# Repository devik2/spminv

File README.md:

# spminv

Simple IGBT motor inverter

Initial idea was independent but in 2024 when I started I borrowed
idea of heatsink from from STMBL project.

There are differences from STMBL, only one MCU located on power N potential,
1xCAN,2xRS422 RX and 2xRS485 RX/TX for encoder/communications and separated
by galvanical isolators.

Flyback power supply for 15V/3V3 on N side and 5V for isolated side. Thus only
input is 90-350V DC.
This is because my main usage is for spindle motors where driver is located near
spindle and not in remote cabinet.

Why not use STMBL ? I wanted to use different IPM, integrate it into CAN network
of my homemade CNC and to play with FOC by myself. 
And I already use my 60V BLDC driver for 3 years and started this "upgrade" before
I found STMBL.

[And have to say, I'd stay with 60V mosfet inverter but it is hard to find quality(!)
 motors. All low ripple hi-torque I found are 200V rated]

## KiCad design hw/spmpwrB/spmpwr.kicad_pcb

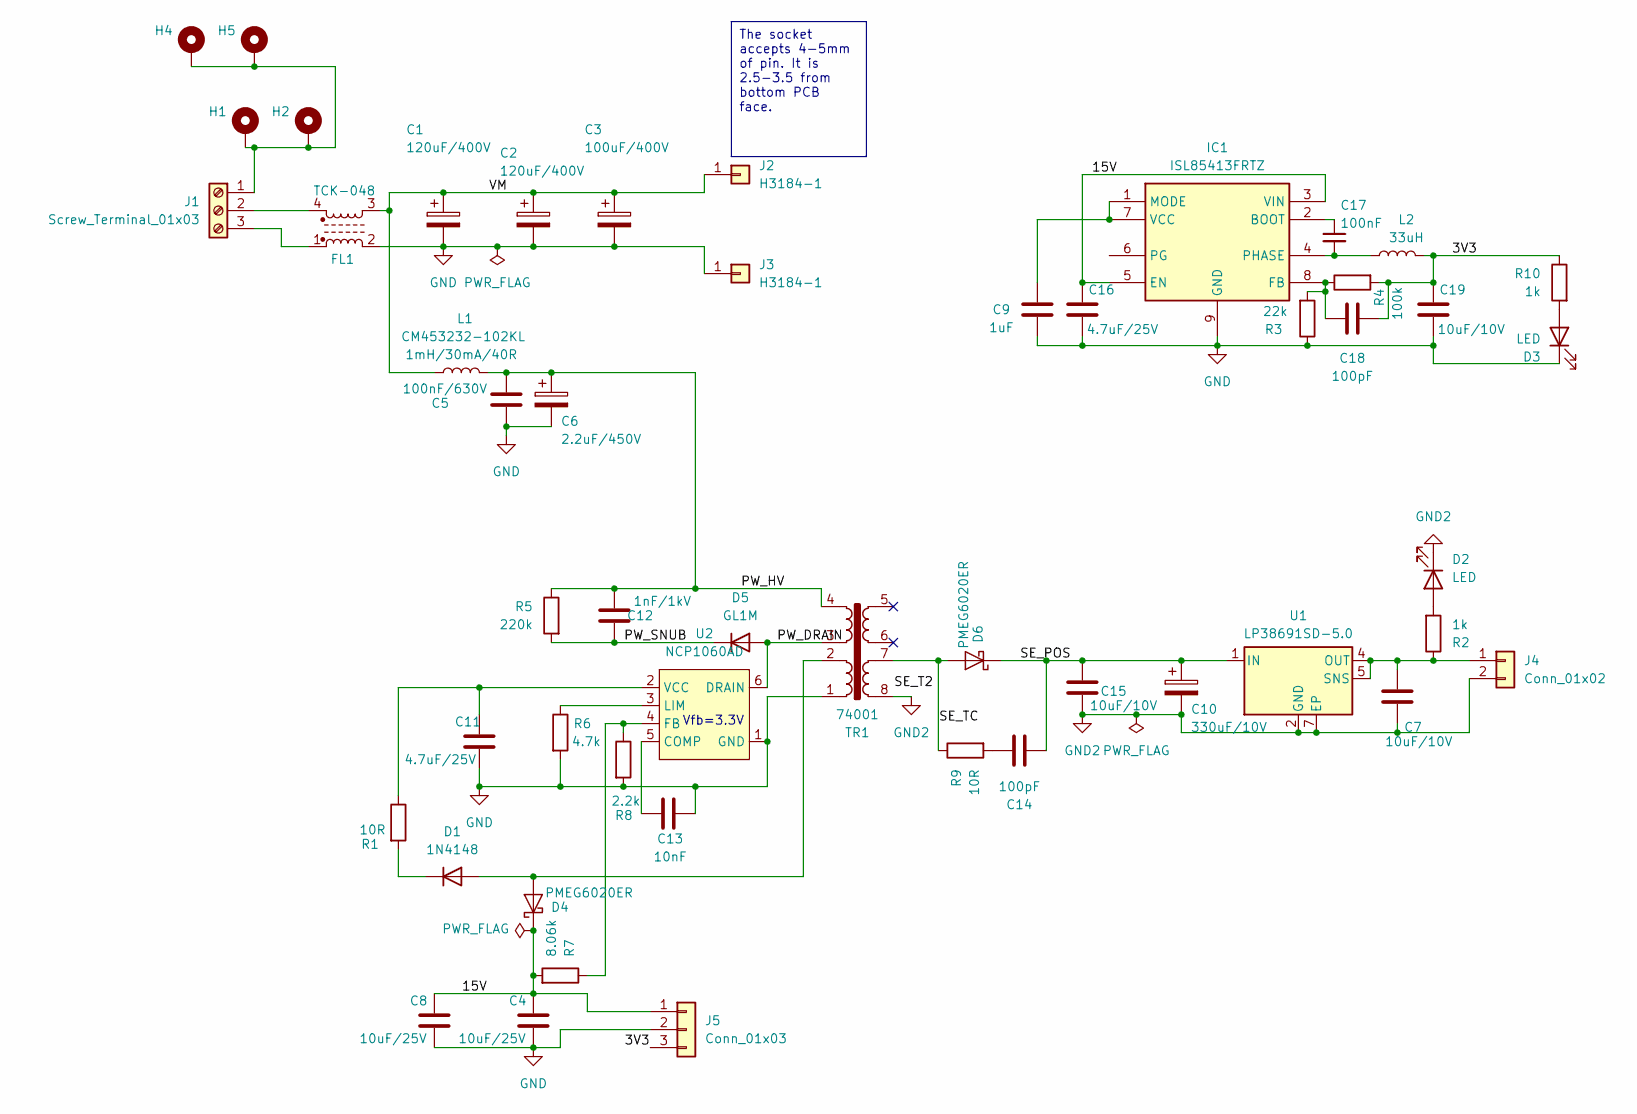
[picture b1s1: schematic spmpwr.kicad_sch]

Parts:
C1, C2: 120uF/400V; CP_Radial_D18.0mm_P7.50mm; Partno 400HXW120MEFR18X
C3: 100uF/400V; CP_Radial_D16.0mm_P7.50mm; Partno 400HXW100MEFR16X
C4, C8: 10uF/25V; C_1206_3216Metric
C5: 100nF/630V; C_1210_3225Metric
C6: 2.2uF/450V; CP_Radial_D6.3mm_P2.50mm
C7, C15, C19: 10uF/10V; C_0805_2012Metric_Pad1.18x1.45mm_HandSolder
C9: 1uF; C_0603_1608Metric_Pad1.08x0.95mm_HandSolder
C10: 330uF/10V; CP_Radial_D6.3mm_P2.50mm; Partno APSE6R3EC3561MF08S
C11, C16: 4.7uF/25V; C_0805_2012Metric_Pad1.18x1.45mm_HandSolder
C12: 1nF/1kV; C_1206_3216Metric_Pad1.33x1.80mm_HandSolder
C13: 10nF; C_0603_1608Metric_Pad1.08x0.95mm_HandSolder
C14, C18: 100pF; C_0603_1608Metric_Pad1.08x0.95mm_HandSolder
C17: 100nF; C_0603_1608Metric
D1: 1N4148; D_MiniMELF
D2, D3: LED; LED_0603_1608Metric
D4, D6: PMEG6020ER; D_SOD-123F
D5: GL1M; D_MiniMELF
FL1: L_Ferrite_Coupled_1243; Choke_common_12.0x12.0mm_P7.62; Partno TCK-048
H1, H2, H4, H5: MountingHole_Pad; MountingHole_3.2mm_M3_DIN965_Pad_TopBottom
IC1: ISL85413FRTZ; WSON-8-1EP_3x3mm_P0.5mm_EP1.2x2mm; Manufacturer_Part_Number ISL85413FRTZ
J1: Screw_Terminal_01x03; Altech_AK300_1x03_P5.00mm_45-Degree
J2, J3: H3184-1; H318401
J4: Conn_01x02; PinHeader_1x02_P2.54mm_Vertical
J5: Conn_01x03; PinHeader_1x03_P2.54mm_Vertical
L1: 1mH/30mA/40R; L_1812_4532Metric_Pad1.30x3.40mm_HandSolder; Partno CM453232-102KL
L2: 33uH; L_Abracon_ASPI-3012S; Partno 74404032330
R1, R9: 10R; R_0603_1608Metric_Pad0.98x0.95mm_HandSolder
R2, R10: 1k; R_0603_1608Metric_Pad0.98x0.95mm_HandSolder
R3: 22k; R_0603_1608Metric_Pad0.98x0.95mm_HandSolder
R4: 100k; R_0603_1608Metric_Pad0.98x0.95mm_HandSolder
R5: 220k; R_1206_3216Metric_Pad1.30x1.75mm_HandSolder
R6: 4.7k; R_0603_1608Metric_Pad0.98x0.95mm_HandSolder
R7: 8.06k; R_0603_1608Metric_Pad0.98x0.95mm_HandSolder
R8: 2.2k; R_0603_1608Metric_Pad0.98x0.95mm_HandSolder
TR1: 74001; Myrra_74000
U1: LP38691SD-5.0; WSON-6-1EP_3x3mm_P0.95mm
U2: NCP1060AD; SSOP-10_3.9x4.9mm_P1.00mm

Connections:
/3V3: C18.1, C19.1, J5.3, L2.2, R4.2, R10.1
/15V: C4.1, C8.1, C16.1, D4.1 (K), IC1.3 (VIN), IC1.5 (EN), J5.1, R7.2
/PW_DRAIN: D5.2 (A), TR1.3, U2.6 (DRAIN), U2.7 (DRAIN), U2.8 (DRAIN), U2.9 (DRAIN), U2.10 (DRAIN)
/PW_HV: C5.1, C6.1, C12.1, L1.2, R5.1, TR1.4
/PW_SNUB: C12.2, D5.1 (K), R5.2
/SE_POS: C10.1, C14.2, C15.1, D6.1 (K), U1.1 (IN), U1.6 (IN)
/SE_TC: D6.2 (A), R9.1, TR1.7
/VM: C1.1, C2.1, C3.1, FL1.3, J2.1, L1.1
GND: C1.2, C2.2, C3.2, C4.2, C5.2, C6.2, C8.2, C9.2, C11.2, C13.2, C16.2, C19.2, D3.1 (K), FL1.2, IC1.9 (GND), J3.1, J5.2, R3.1, R6.2, R8.2, TR1.1, U2.1 (GND)
GND2: C7.2, C10.2, C15.2, D2.1 (K), J4.2, TR1.8, U1.2 (GND), U1.7 (EP)
unnamed: C14.1, R9.2
unnamed: D1.2 (A), D4.2 (A), TR1.2
unnamed: D1.1 (K), R1.2
unnamed: D2.2 (A), R2.2
unnamed: D3.2 (A), R10.2
unnamed: C17.1, IC1.2 (BOOT)
unnamed: C18.2, IC1.8 (FB), R3.2, R4.1
unnamed: C9.1, IC1.1 (MODE), IC1.7 (VCC)
unnamed: C17.2, IC1.4 (PHASE), L2.1
unnamed: H1.1, H2.1, H4.1, H5.1, J1.1
unnamed: FL1.4, J1.2
unnamed: FL1.1, J1.3
unnamed: C7.1, J4.1, R2.1, U1.4 (OUT), U1.5 (SNS)
unnamed: C13.1, U2.5 (COMP)
unnamed: R7.1, R8.1, U2.4 (FB)
unnamed: R6.1, U2.3 (LIM)
unnamed: C11.1, R1.1, U2.2 (VCC)

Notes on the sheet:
The socket accepts 4-5mm of pin. It is 2.5-3.5 from bottom PCB face.
Vfb=3.3V

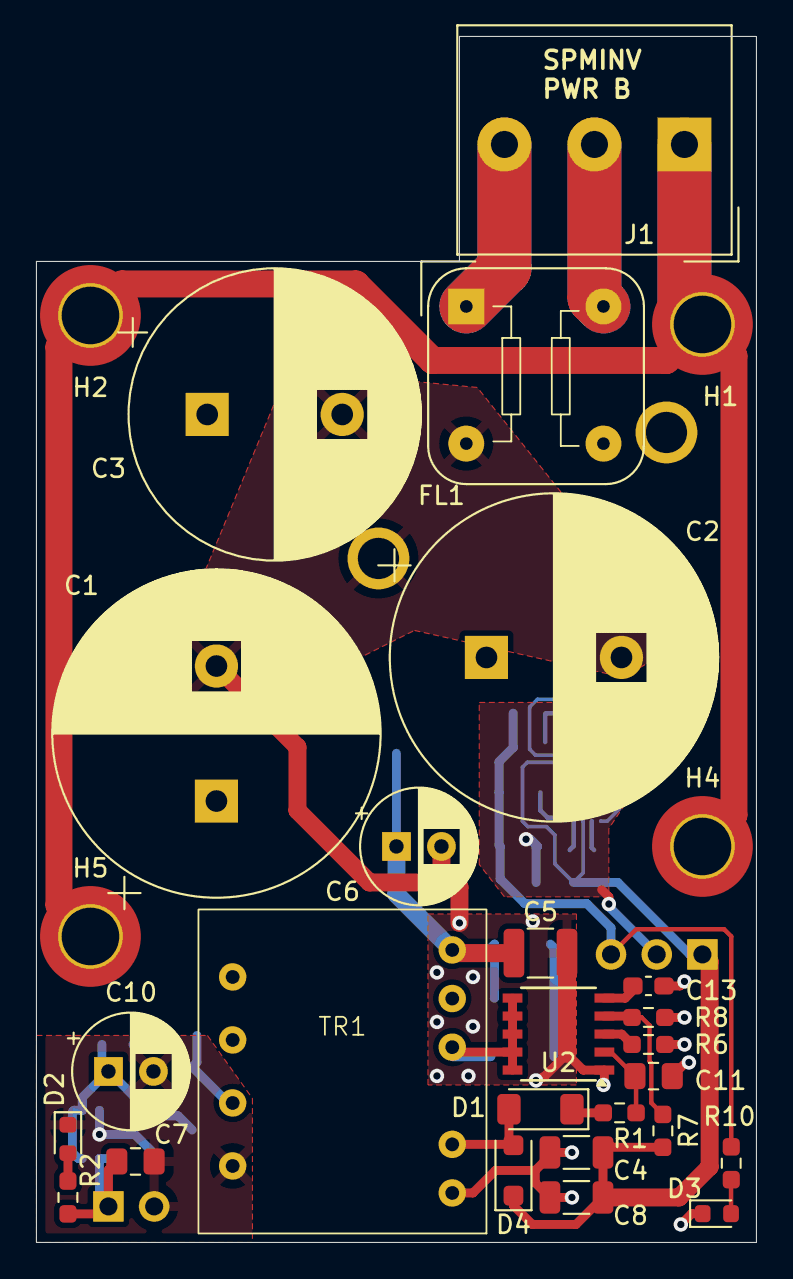
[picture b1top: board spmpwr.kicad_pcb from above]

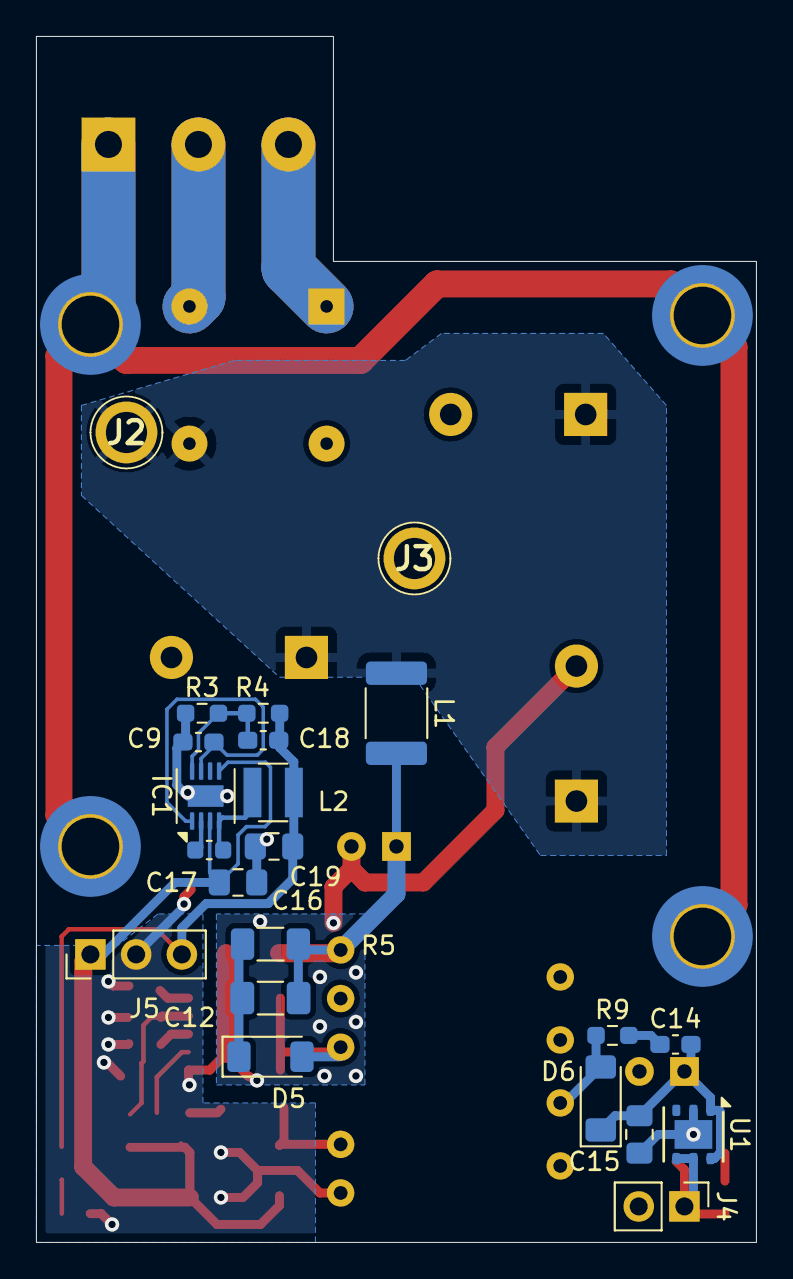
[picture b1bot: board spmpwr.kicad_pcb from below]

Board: 2 copper layers, 40.0 x 67.0 mm, 51 parts (22 on the bottom side), 27 nets.

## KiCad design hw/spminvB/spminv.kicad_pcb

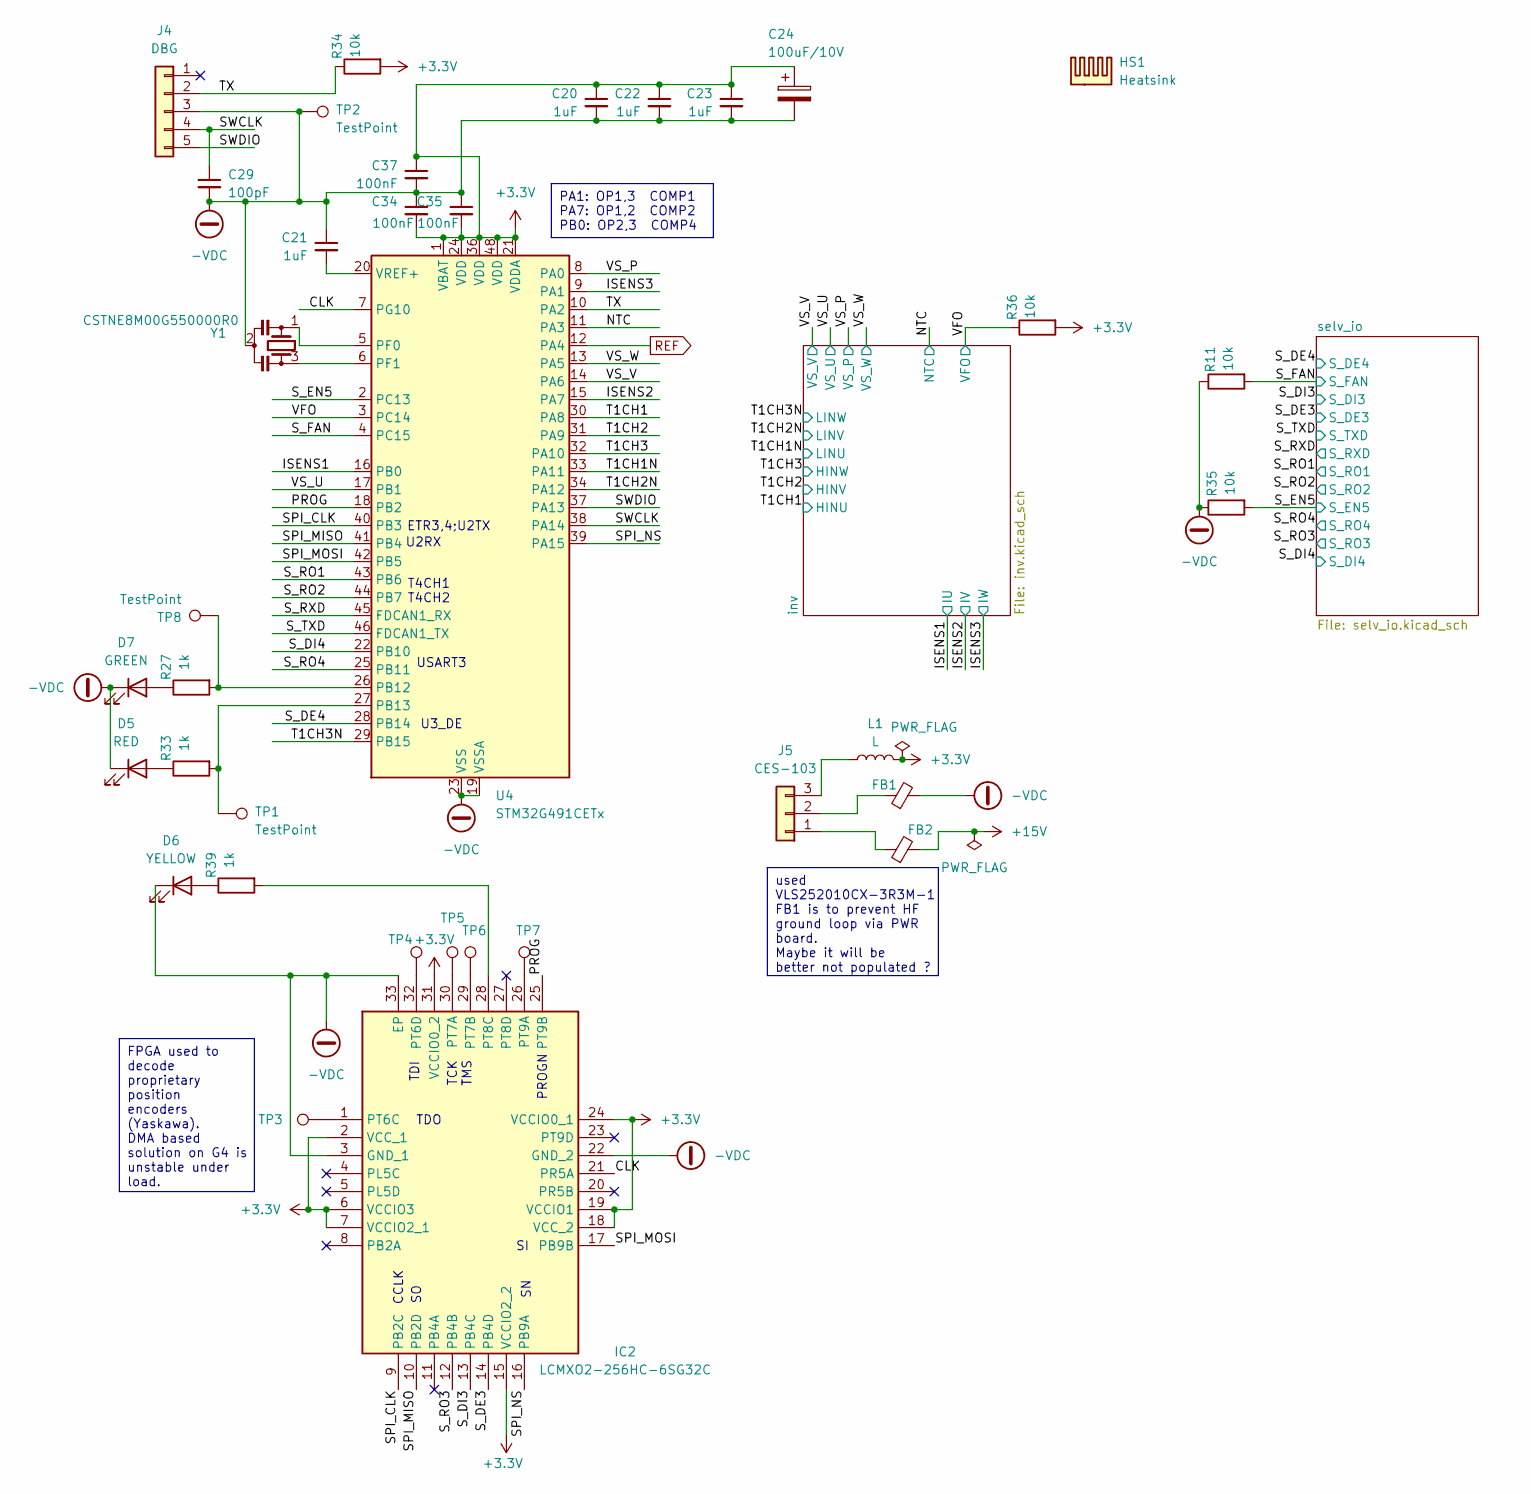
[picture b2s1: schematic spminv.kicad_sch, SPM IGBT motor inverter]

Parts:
C20, C21, C22, C23: 1uF; C_0603_1608Metric_Pad1.08x0.95mm_HandSolder
C24: 100uF/10V; CP_EIA-6032-28_Kemet-C
C29: 100pF; C_0603_1608Metric_Pad1.08x0.95mm_HandSolder
C34, C35, C37: 100nF; C_0603_1608Metric_Pad1.08x0.95mm_HandSolder
D5: RED; LED_0603_1608Metric
D6: YELLOW; LED_0603_1608Metric
D7: GREEN; LED_0603_1608Metric
FB1, FB2: FerriteBead_Small; L_1206_3216Metric
HS1: Heatsink; Heatsink_Stonecold_HS-S03_13.21x12.7mm
IC2: LCMXO2-256HC-6SG32C; QFN-32-1EP_5x5mm_P0.5mm_EP3.3x3.3mm; Manufacturer_Part_Number LCMXO2-256HC-6SG32C; Mouser Part Number 842-MXO2-256HC6SG32C
J4: DBG; Molex_PicoBlade_53048-0510_1x05_P1.25mm_Horizontal
J5: CES-103; PinSocket_1x03_P2.54mm_Vertical
L1: L; L_1206_3216Metric
R11, R34, R35, R36: 10k; R_0603_1608Metric_Pad0.98x0.95mm_HandSolder
R27, R33, R39: 1k; R_0603_1608Metric_Pad0.98x0.95mm_HandSolder
TP1, TP2, TP3, TP4, TP5, TP6, TP7, TP8: TestPoint; TestPoint_THTPad_D1.0mm_Drill0.5mm
U4: STM32G491CETx; LQFP-48_7x7mm_P0.5mm
Y1: CSTNE8M00G550000R0; Resonator_SMD_Murata_CSTxExxV-3Pin_3.0x1.1mm

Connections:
+3.3V: C20.1, C22.1, C23.1, C24.1, C34.2, C35.2, C37.1, IC2.2 (VCC_1), IC2.6 (VCCIO3), IC2.7 (VCCIO2_1), IC2.15 (VCCIO2_2), IC2.18 (VCC_2), IC2.19 (VCCIO1), IC2.24 (VCCIO0_1), IC2.31 (VCCIO0_2), L1.2, R34.2, R36.2, U4.1 (VBAT), U4.21 (VDDA), U4.24 (VDD), U4.36 (VDD), U4.48 (VDD); also elsewhere on the board
+15V: FB2.2; also elsewhere on the board
-VDC: C20.2, C21.1, C22.2, C23.2, C24.2, C29.2, C34.1, C35.1, C37.2, D5.1 (K), D6.1 (K), D7.1 (K), FB1.2, IC2.3 (GND_1), IC2.22 (GND_2), IC2.33 (EP), J4.3, R11.1, R35.1, TP2.1, U4.19 (VSSA), U4.23 (VSS), U4.35 (VSS), U4.47 (VSS), Y1.2; also elsewhere on the board
/CLK: IC2.21 (PR5A), U4.7 (PG10)
/ISENS1: U4.16 (PB0); also elsewhere on the board
/ISENS2: U4.15 (PA7); also elsewhere on the board
/ISENS3: U4.9 (PA1); also elsewhere on the board
/NTC: U4.11 (PA3); also elsewhere on the board
/PROG: IC2.25 (PT9B), U4.18 (PB2)
/SPI_CLK: IC2.9 (PB2C), U4.40 (PB3)
/SPI_MISO: IC2.10 (PB2D), U4.41 (PB4)
/SPI_MOSI: IC2.17 (PB9B), U4.42 (PB5)
/SPI_NS: IC2.16 (PB9A), U4.39 (PA15)
/SWCLK: C29.1, J4.4, U4.38 (PA14)
/SWDIO: J4.5, U4.37 (PA13)
/S_DE3: IC2.14 (PB4D); also elsewhere on the board
/S_DE4: U4.28 (PB14); also elsewhere on the board
/S_DI3: IC2.13 (PB4C); also elsewhere on the board
/S_DI4: U4.22 (PB10); also elsewhere on the board
/S_EN5: R35.2, U4.2 (PC13); also elsewhere on the board
/S_FAN: R11.2, U4.4 (PC15); also elsewhere on the board
/S_RO1: U4.43 (PB6); also elsewhere on the board
/S_RO2: U4.44 (PB7); also elsewhere on the board
/S_RO3: IC2.12 (PB4B); also elsewhere on the board
/S_RO4: U4.25 (PB11); also elsewhere on the board
/S_RXD: U4.45 (FDCAN1_RX); also elsewhere on the board
/S_TXD: U4.46 (FDCAN1_TX); also elsewhere on the board
/T1CH1: U4.30 (PA8); also elsewhere on the board
/T1CH1N: U4.33 (PA11); also elsewhere on the board
/T1CH2: U4.31 (PA9); also elsewhere on the board
/T1CH2N: U4.34 (PA12); also elsewhere on the board
/T1CH3: U4.32 (PA10); also elsewhere on the board
/T1CH3N: U4.29 (PB15); also elsewhere on the board
/TX: J4.2, R34.1, U4.10 (PA2)
/VFO: R36.1, U4.3 (PC14); also elsewhere on the board
/VS_P: U4.8 (PA0); also elsewhere on the board
/VS_U: U4.17 (PB1); also elsewhere on the board
/VS_V: U4.14 (PA6); also elsewhere on the board
/VS_W: U4.13 (PA5); also elsewhere on the board
unnamed: D5.2 (A), R33.1
unnamed: D6.2 (A), R39.1
unnamed: D7.2 (A), R27.1
unnamed: IC2.1 (PT6C), TP3.1
unnamed: IC2.32 (PT6D), TP4.1
unnamed: IC2.30 (PT7A), TP5.1
unnamed: IC2.29 (PT7B), TP6.1
unnamed: IC2.28 (PT8C), R39.2
unnamed: IC2.26 (PT9A), TP7.1
unnamed: FB2.1, J5.1
unnamed: FB1.1, J5.2
unnamed: J5.3, L1.1
unnamed: R27.2, TP8.1, U4.26 (PB12)
unnamed: R33.2, TP1.1, U4.27 (PB13)
unnamed: U4.5 (PF0), Y1.1
unnamed: U4.6 (PF1), Y1.3
unnamed: C21.2, U4.20 (VREF+)
REF: U4.12 (PA4); also elsewhere on the board

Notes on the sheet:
PA1: OP1,3 COMP1 PA7: OP1,2 COMP2 PB0: OP2,3 COMP4
FPGA used to decode proprietary position encoders (Yaskawa). DMA based solution on G4 is unstable under load.
used VLS252010CX-3R3M-1 FB1 is to prevent HF ground loop via PWR board. Maybe it will be better not populated ?
TDI
PROGN
TDO
USART3
T4CH1 T4CH2
TCK TMS
U2RX
ETR3,4;U2TX
U3_DE
CCLK

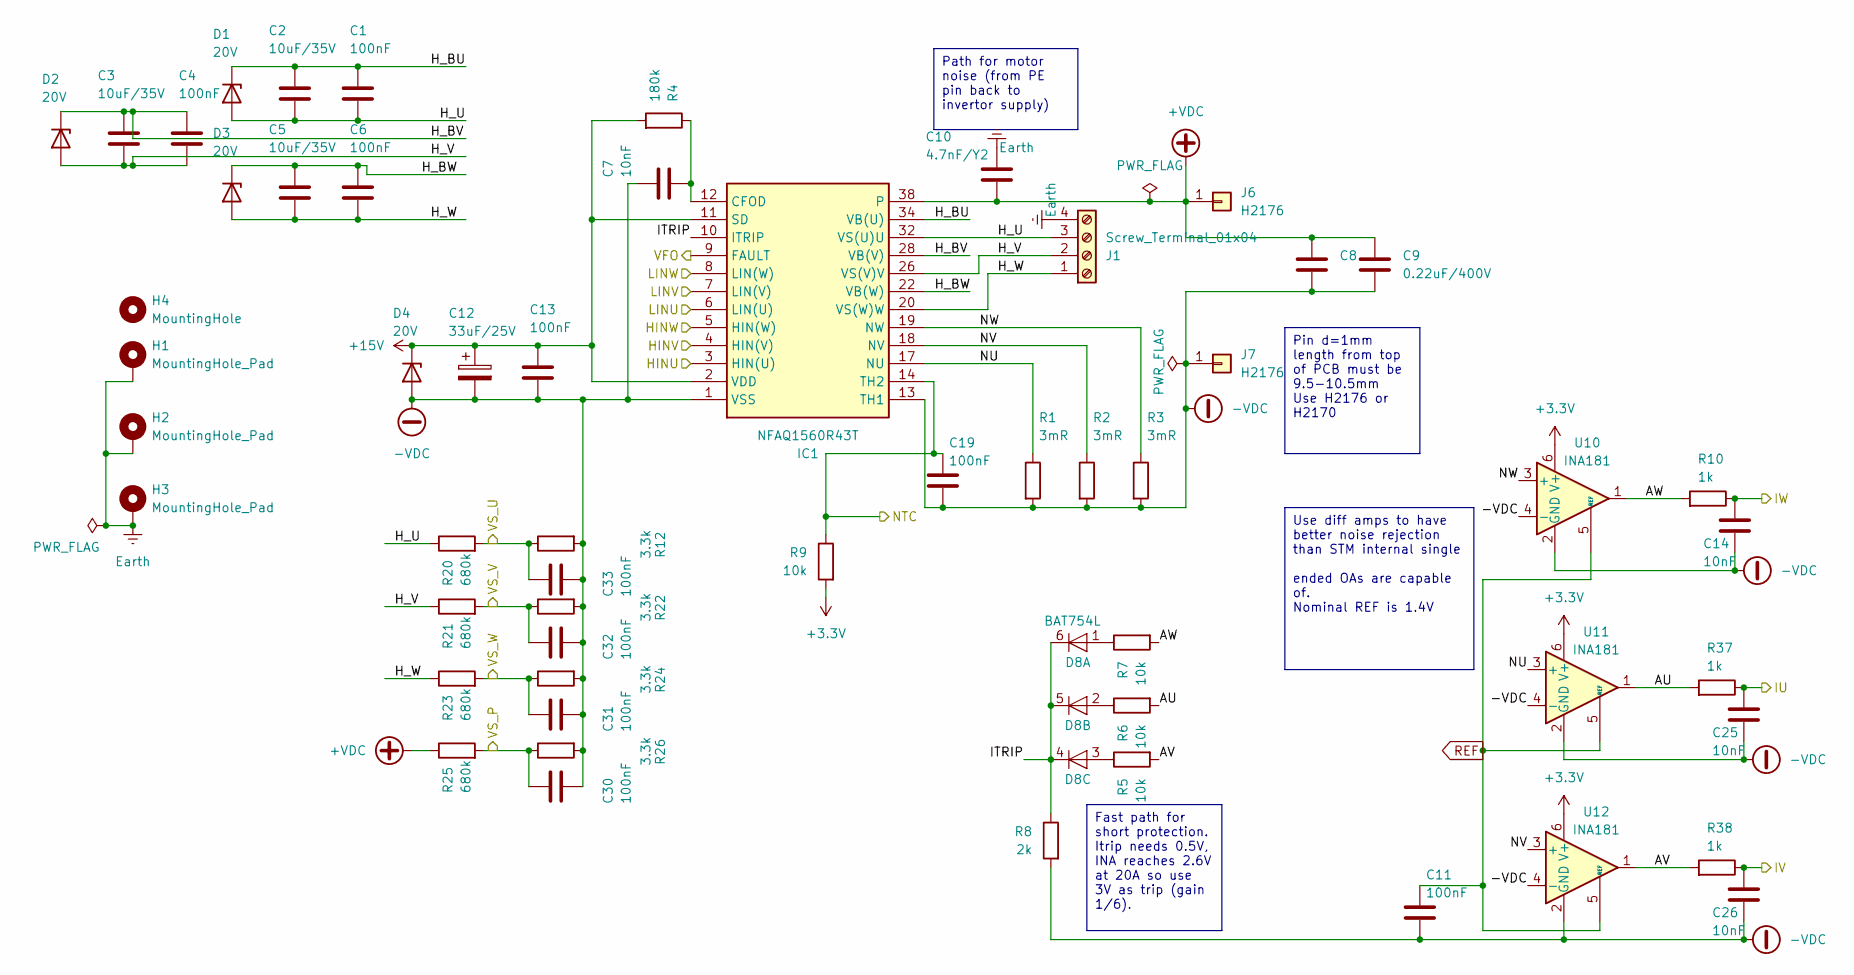
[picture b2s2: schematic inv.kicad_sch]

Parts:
C1, C4, C6, C11, C13, C19, C30, C31, C32, C33: 100nF; C_0603_1608Metric
C2, C3, C5: 10uF/35V; C_1210_3225Metric
C7, C14, C25, C26: 10nF; C_0603_1608Metric
C8, C9: 0.22uF/400V; C_2220_5750Metric_Pad1.97x5.40mm_HandSolder
C10: 4.7nF/Y2; C_2220_5750Metric
C12: 33uF/25V; CP_EIA-6032-28_Kemet-C
D1, D2, D3, D4: 20V; D_MiniMELF; Partno BZV55C20
D8: BAT754L; SOT-363_SC-70-6
H1, H2, H3: MountingHole_Pad; MountingHole_3.2mm_M3_DIN965_Pad_TopBottom
H4: MountingHole; MountingHole_3.2mm_M3_DIN965
IC1: NFAQ1560R43T; Manufacturer_Part_Number NFAQ1560R43T; Mouser Part Number 863-NFAQ1560R43T
J1: Screw_Terminal_01x04; Altech_AK300_1x04_P5.00mm_45-Degree
J6, J7: H2176; Pin_D1.3mm_L11.0mm
R1, R2, R3: 3mR; R_1206_3216Metric
R4: 180k; R_0603_1608Metric_Pad0.98x0.95mm_HandSolder
R5, R6, R7, R9: 10k; R_0603_1608Metric_Pad0.98x0.95mm_HandSolder
R8: 2k; R_0603_1608Metric_Pad0.98x0.95mm_HandSolder
R10, R37, R38: 1k; R_0603_1608Metric_Pad0.98x0.95mm_HandSolder
R12, R22, R24, R26: 3.3k; R_0603_1608Metric_Pad0.98x0.95mm_HandSolder
R20, R21, R23, R25: 680k; R_MiniMELF_MMA-0204
U10, U11, U12: INA181; SOT-363_SC-70-6

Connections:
+3.3V: R9.2, U10.6 (V+), U11.6 (V+), U12.6 (V+); also elsewhere on the board
+15V: C12.1, C13.1, D4.1 (K), IC1.2 (VDD), IC1.11 (SD), R4.2; also elsewhere on the board
+VDC: C8.1, C9.1, C10.2, IC1.38, J6.1, R25.1
-VDC: C7.1, C8.2, C9.2, C11.2, C12.2, C13.2, C14.2, C19.2, C25.2, C26.2, C30.2, C31.2, C32.2, C33.2, D4.2 (A), IC1.1 (VSS), IC1.13 (TH1), J7.1, R1.2, R2.2, R3.2, R8.2, R12.2, R22.2, R24.2, R26.2, U10.2 (GND), U10.4 (-), U11.2 (GND), U11.4 (-), U12.2 (GND), U12.4 (-); also elsewhere on the board
/ISENS1: C25.1, R37.1; also elsewhere on the board
/ISENS2: C26.1, R38.1; also elsewhere on the board
/ISENS3: C14.1, R10.1; also elsewhere on the board
/NTC: C19.1, IC1.14 (TH2), R9.1; also elsewhere on the board
/T1CH1: IC1.3 (HIN(U)); also elsewhere on the board
/T1CH1N: IC1.6 (LIN(U)); also elsewhere on the board
/T1CH2: IC1.4 (HIN(V)); also elsewhere on the board
/T1CH2N: IC1.7 (LIN(V)); also elsewhere on the board
/T1CH3: IC1.5 (HIN(W)); also elsewhere on the board
/T1CH3N: IC1.8 (LIN(W)); also elsewhere on the board
/VFO: IC1.9 (FAULT); also elsewhere on the board
/VS_P: C30.1, R25.2, R26.1; also elsewhere on the board
/VS_U: C33.1, R12.1, R20.2; also elsewhere on the board
/VS_V: C32.1, R21.2, R22.1; also elsewhere on the board
/VS_W: C31.1, R23.2, R24.1; also elsewhere on the board
/inv/AU: R6.2, R37.2, U11.1
/inv/AV: R5.2, R38.2, U12.1
/inv/AW: R7.2, R10.2, U10.1
/inv/H_BU: C1.1, C2.1, D1.1 (K), IC1.34 (VB(U))
/inv/H_BV: C3.1, C4.1, D2.1 (K), IC1.28 (VB(V))
/inv/H_BW: C5.1, C6.1, D3.1 (K), IC1.22 (VB(W))
/inv/H_U: C1.2, C2.2, D1.2 (A), IC1.32 (VS(U)U), J1.3, R20.1
/inv/H_V: C3.2, C4.2, D2.2 (A), IC1.26 (VS(V)V), J1.2, R21.1
/inv/H_W: C5.2, C6.2, D3.2 (A), IC1.20 (VS(W)W), J1.1, R23.1
/inv/ITRIP: D8.4 (K), D8.5 (K), D8.6 (K), IC1.10 (ITRIP), R8.1
/inv/NU: IC1.17 (NU), R1.1, U11.3 (+)
/inv/NV: IC1.18 (NV), R2.1, U12.3 (+)
/inv/NW: IC1.19 (NW), R3.1, U10.3 (+)
Earth: C10.1, H1.1, H2.1, H3.1, J1.4
unnamed: D8.1 (A), R7.1
unnamed: D8.2 (A), R6.1
unnamed: D8.3 (A), R5.1
unnamed: C7.2, IC1.12 (CFOD), R4.1
REF: C11.1, U10.5 (REF), U11.5 (REF), U12.5 (REF); also elsewhere on the board

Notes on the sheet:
Pin d=1mm length from top of PCB must be 9.5-10.5mm Use H2176 or H2170
Fast path for short protection. Itrip needs 0.5V, INA reaches 2.6V at 20A so use 3V as trip (gain 1/6).
Use diff amps to have better noise rejection than STM internal single ended OAs are capable of. Nominal REF is 1.4V
Path for motor noise (from PE pin back to invertor supply)

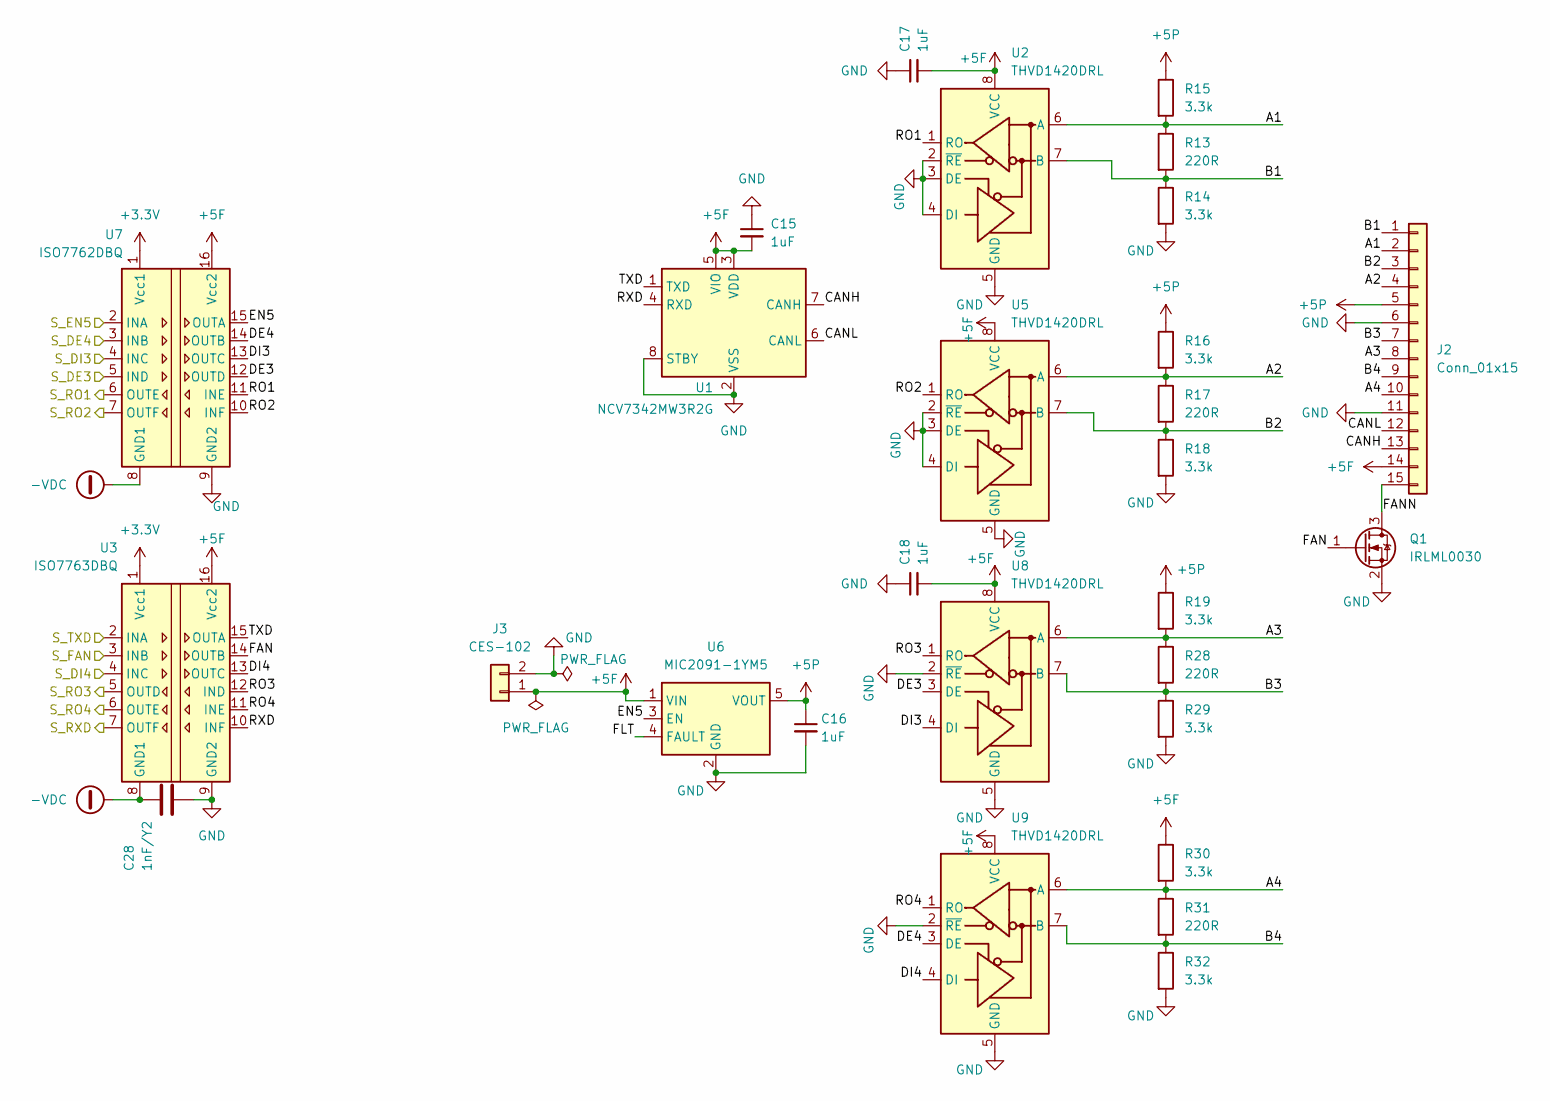
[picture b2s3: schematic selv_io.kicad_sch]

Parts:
C15, C16, C17, C18: 1uF; C_0603_1608Metric_Pad1.08x0.95mm_HandSolder
C28: 1nF/Y2; C_2220_5750Metric
J2: Conn_01x15; CUI_TBL009V-254-15BE-2BE
J3: CES-102; PinSocket_1x02_P2.54mm_Vertical
Q1: IRLML0030; SOT-23
R13, R17, R28, R31: 220R; R_0805_2012Metric
R14, R15, R16, R18, R19, R29, R30, R32: 3.3k; R_0805_2012Metric
U1: NCV7342MW3R2G; DFN-8-1EP_3x3mm_P0.65mm_EP1.55x2.4mm
U2, U5, U8, U9: THVD1420DRL; Texas_VSON-HR-8_1.5x2mm_P0.5mm
U3: ISO7763DBQ; SSOP-16_3.9x4.9mm_P0.635mm
U6: MIC2091-1YM5; SOT-23-5
U7: ISO7762DBQ; SSOP-16_3.9x4.9mm_P0.635mm

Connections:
+3.3V: U3.1 (Vcc1), U7.1 (Vcc1); also elsewhere on the board
+5F: C15.2, C17.2, C18.2, J2.14, J3.1, R30.1, U1.3 (VDD), U1.5 (VIO), U2.8 (VCC), U3.16 (Vcc2), U5.8 (VCC), U6.1 (VIN), U7.16 (Vcc2), U8.8 (VCC), U9.8 (VCC)
+5P: C16.1, J2.5, R15.1, R16.1, R19.1, U6.5 (VOUT)
-VDC: C28.1, U3.8 (GND1), U7.8 (GND1); also elsewhere on the board
/S_DE3: U7.5 (IND); also elsewhere on the board
/S_DE4: U7.3 (INB); also elsewhere on the board
/S_DI3: U7.4 (INC); also elsewhere on the board
/S_DI4: U3.4 (INC); also elsewhere on the board
/S_EN5: U7.2 (INA); also elsewhere on the board
/S_FAN: U3.3 (INB); also elsewhere on the board
/S_RO1: U7.6 (OUTE); also elsewhere on the board
/S_RO2: U7.7 (OUTF); also elsewhere on the board
/S_RO3: U3.5 (OUTD); also elsewhere on the board
/S_RO4: U3.6 (OUTE); also elsewhere on the board
/S_RXD: U3.7 (OUTF); also elsewhere on the board
/S_TXD: U3.2 (INA); also elsewhere on the board
/selv_io/A1: J2.2, R13.1, R15.2, U2.6 (A)
/selv_io/A2: J2.4, R16.2, R17.1, U5.6 (A)
/selv_io/A3: J2.8, R19.2, R28.1, U8.6 (A)
/selv_io/A4: J2.10, R30.2, R31.1, U9.6 (A)
/selv_io/B1: J2.1, R13.2, R14.1, U2.7 (B)
/selv_io/B2: J2.3, R17.2, R18.1, U5.7 (B)
/selv_io/B3: J2.7, R28.2, R29.1, U8.7 (B)
/selv_io/B4: J2.9, R31.2, R32.1, U9.7 (B)
/selv_io/CANH: J2.13, U1.7 (CANH)
/selv_io/CANL: J2.12, U1.6 (CANL)
/selv_io/DE3: U7.12 (OUTD), U8.3 (DE)
/selv_io/DE4: U7.14 (OUTB), U9.3 (DE)
/selv_io/DI3: U7.13 (OUTC), U8.4 (DI)
/selv_io/DI4: U3.13 (OUTC), U9.4 (DI)
/selv_io/EN5: U6.3 (EN), U7.15 (OUTA)
/selv_io/FAN: Q1.1 (G), U3.14 (OUTB)
/selv_io/FANN: J2.15, Q1.3 (D)
/selv_io/FLT: U6.4 (FAULT)
/selv_io/RO1: U2.1 (RO), U7.11 (INE)
/selv_io/RO2: U5.1 (RO), U7.10 (INF)
/selv_io/RO3: U3.12 (IND), U8.1 (RO)
/selv_io/RO4: U3.11 (INE), U9.1 (RO)
/selv_io/RXD: U1.4 (RXD), U3.10 (INF)
/selv_io/TXD: U1.1 (TXD), U3.15 (OUTA)
GND: C15.1, C16.2, C17.1, C18.1, C28.2, J2.6, J2.11, J3.2, Q1.2 (S), R14.2, R18.2, R29.2, R32.2, U1.2 (VSS), U1.8 (STBY), U1.9 (VSS), U2.2 (~RE), U2.3 (DE), U2.4 (DI), U2.5 (GND), U3.9 (GND2), U5.2 (~RE), U5.3 (DE), U5.4 (DI), U5.5 (GND), U6.2 (GND), U7.9 (GND2), U8.2 (~RE), U8.5 (GND), U9.2 (~RE), U9.5 (GND)

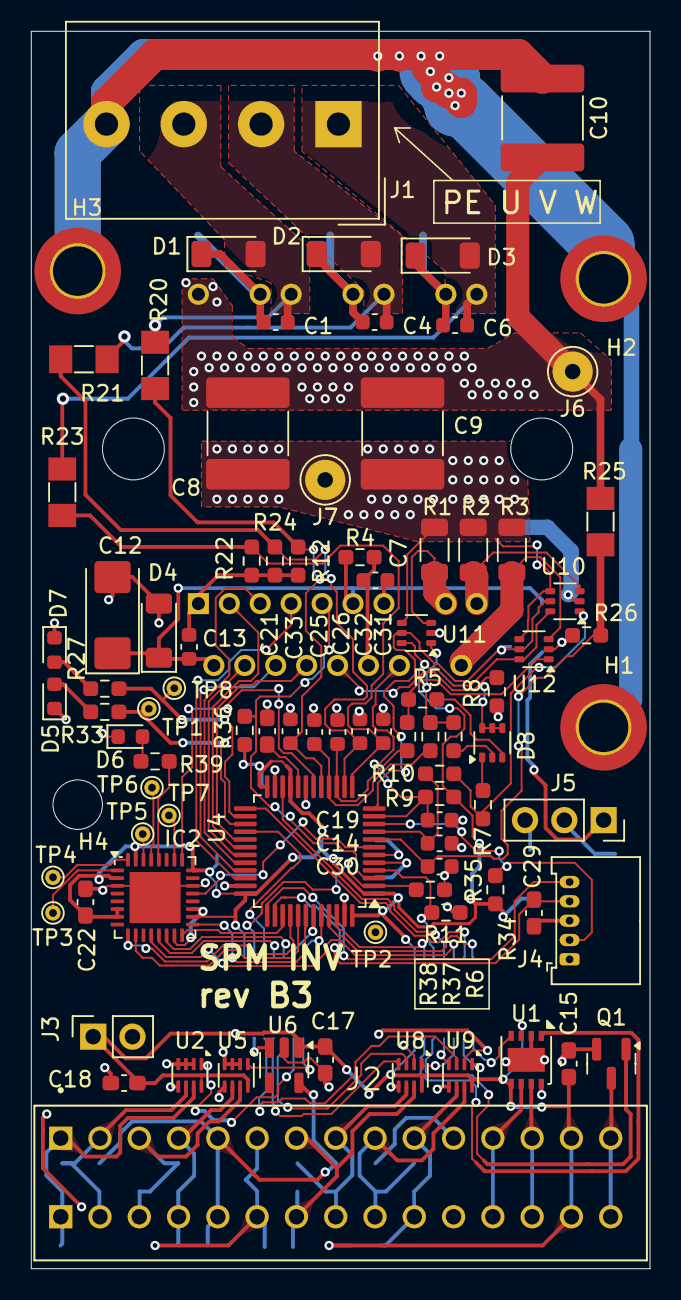
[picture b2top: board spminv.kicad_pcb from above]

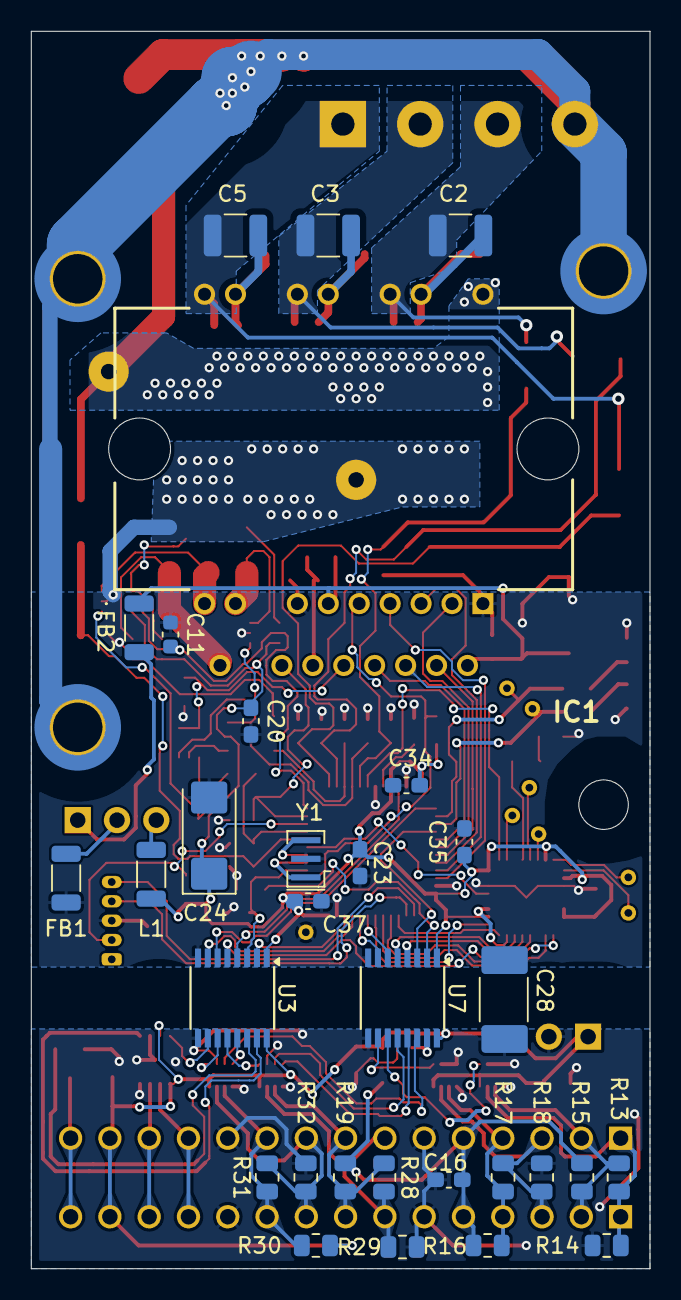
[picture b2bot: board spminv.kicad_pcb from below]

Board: 2 copper layers, 40.0 x 80.0 mm, 120 parts (31 on the bottom side), 102 nets.

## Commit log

2024-12-12 Initial commit of HW
2024-12-12 More comlete README
2024-12-12 README update
